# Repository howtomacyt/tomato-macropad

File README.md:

# tomato-macropad
This is my macropad that I somehow spent nearly 4 straight days designing!!!  
Felt very torturous at times but I am glad it's over and I've got something to show for all that work (hopefully)

## Features ##
9 customisable keys, 1 rotary encoder, 1 OLED Screen. 
Connect via USB-C. 

## CAD Model ##
Everything fits together using 4 M3 Bolts and heatset inserts. 4 for the case and PCB. 
It has 2 separate printed pieces.

**V2:**

## PCB ##
Experimented with RGB lights, but decided not to include them due to the added complexity in tracing. I also had difficulties implementing the firmware for it. 
I may consider switching to KMK. 

## Firmware ##
This hackpad uses QMK firmware. The keys are customisable. 

## Bill of Materials ##

- 9x Cherry MX Switches
- 9x DSA Keycaps
- 4x M3x5x4 Heatset inserts
- 4x M3x16mm SHCS Bolts
- 9x 1N4148 DO-35 Diodes
- 1x 0.91" 128x32 OLED Display
- 1x EC11 Rotary Encoder
- 1x XIAO RP2040

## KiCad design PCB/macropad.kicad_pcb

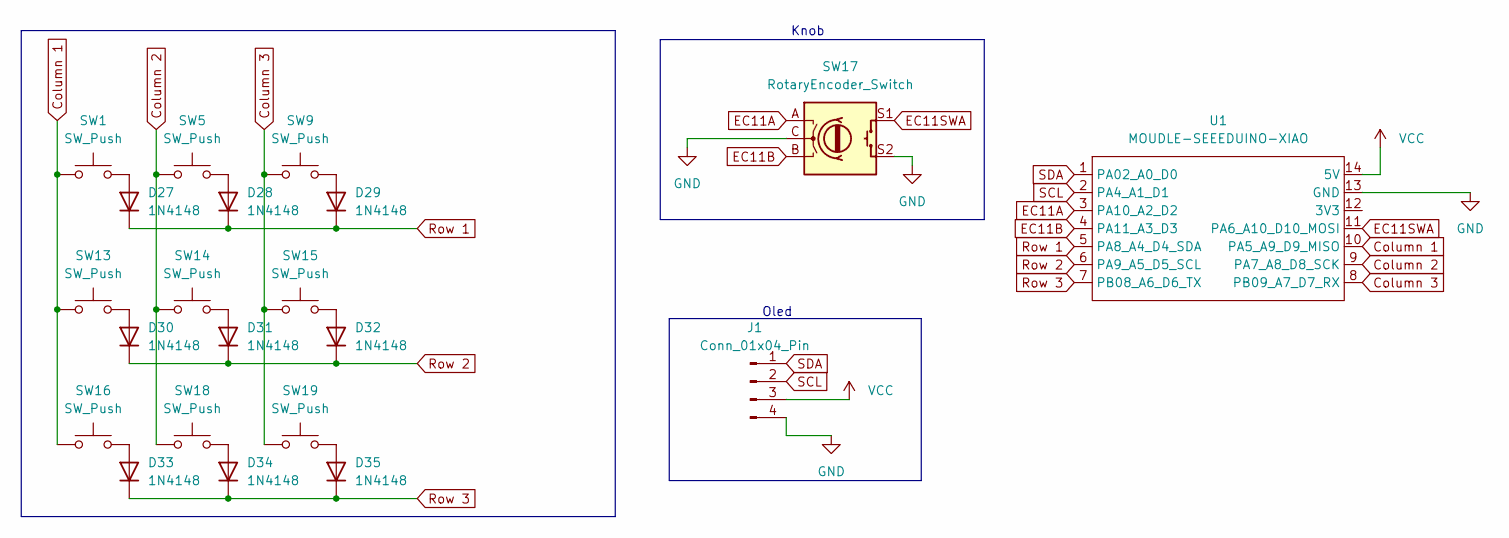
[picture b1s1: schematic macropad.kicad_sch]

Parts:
D27, D28, D29, D30, D31, D32, D33, D34, D35: 1N4148; D_DO-35_SOD27_P7.62mm_Horizontal
J1: Conn_01x04_Pin; PinHeader_1x04_P2.54mm_Vertical
SW1, SW5, SW9, SW13, SW14, SW15, SW16, SW18, SW19: SW_Push; SW_Cherry_MX_1.00u_PCB
SW17: RotaryEncoder_Switch; RotaryEncoder_Alps_EC11E-Switch_Vertical_H20mm
U1: MOUDLE-SEEEDUINO-XIAO; XIAO-Generic-Hybrid-14P-2.54-21X17.8MM

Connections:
Column 1: SW1.1, SW13.1, SW16.1, U1.10 (PA5_A9_D9_MISO)
Column 2: SW5.1, SW14.1, SW18.1, U1.9 (PA7_A8_D8_SCK)
Column 3: SW9.1, SW15.1, SW19.1, U1.8 (PB09_A7_D7_RX)
EC11A: SW17.A, U1.3 (PA10_A2_D2)
EC11B: SW17.B, U1.4 (PA11_A3_D3)
EC11SWA: SW17.S1, U1.11 (PA6_A10_D10_MOSI)
GND: J1.4, SW17.C, SW17.S2, U1.13 (GND)
unnamed: D27.2 (A), SW1.2
unnamed: D28.2 (A), SW5.2
unnamed: D29.2 (A), SW9.2
unnamed: D30.2 (A), SW13.2
unnamed: D31.2 (A), SW14.2
unnamed: D32.2 (A), SW15.2
unnamed: D33.2 (A), SW16.2
unnamed: D34.2 (A), SW18.2
unnamed: D35.2 (A), SW19.2
Row 1: D27.1 (K), D28.1 (K), D29.1 (K), U1.5 (PA8_A4_D4_SDA)
Row 2: D30.1 (K), D31.1 (K), D32.1 (K), U1.6 (PA9_A5_D5_SCL)
Row 3: D33.1 (K), D34.1 (K), D35.1 (K), U1.7 (PB08_A6_D6_TX)
SCL: J1.2, U1.2 (PA4_A1_D1)
SDA: J1.1, U1.1 (PA02_A0_D0)
VCC: J1.3, U1.14 (5V)

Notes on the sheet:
Oled
Knob

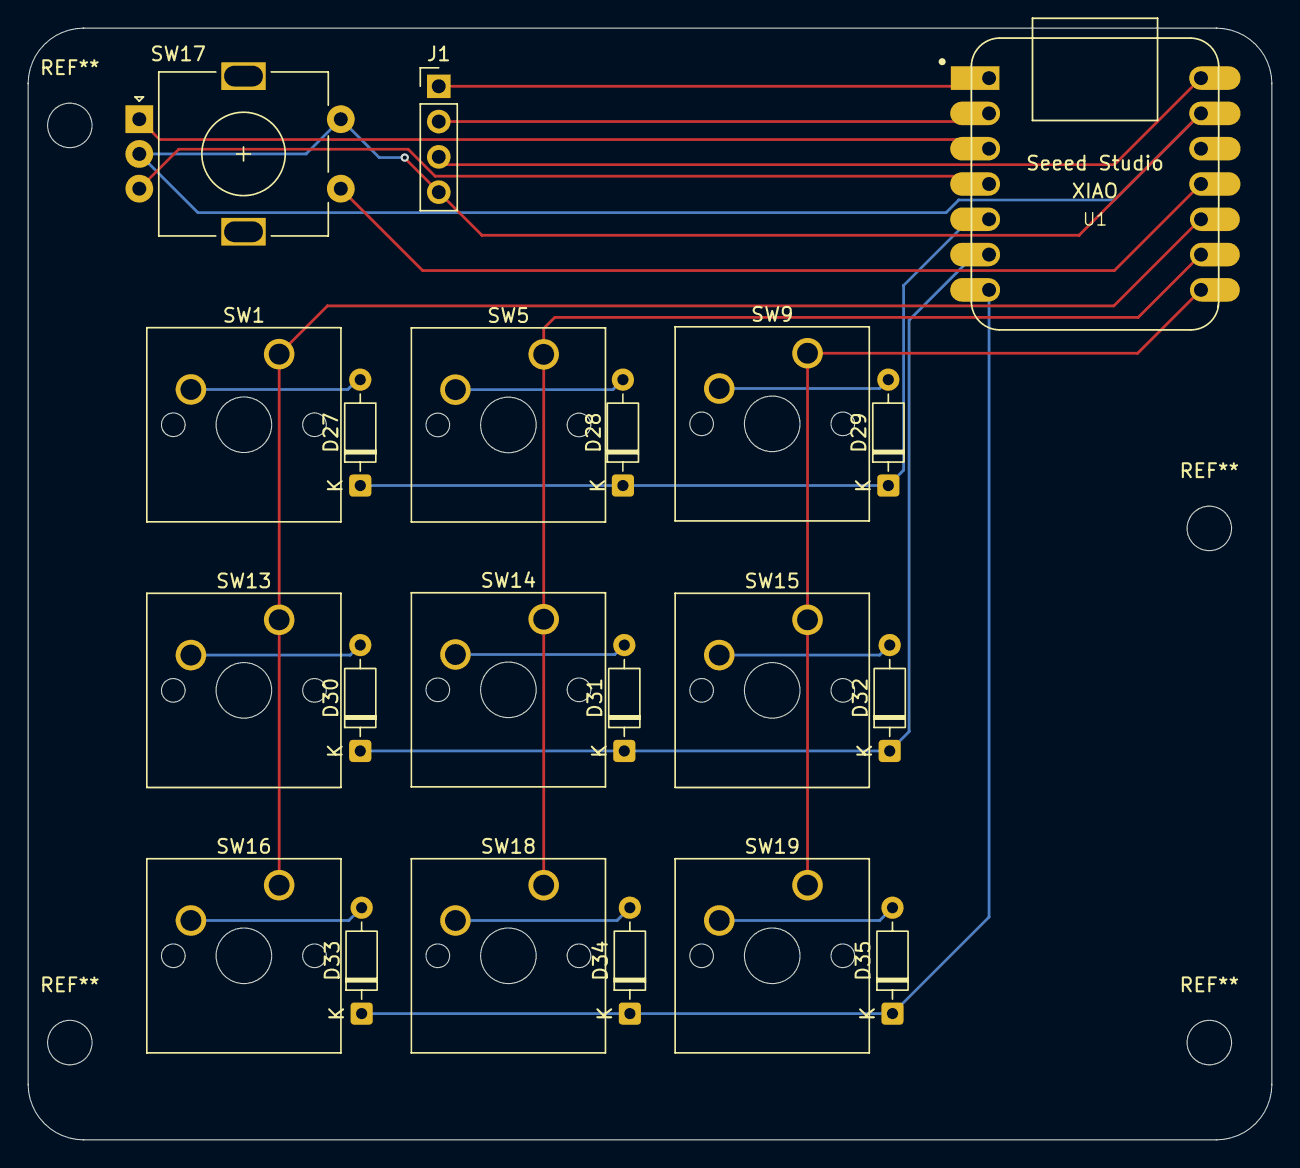
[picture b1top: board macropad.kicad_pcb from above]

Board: 2 copper layers, 89.5 x 80.0 mm, 21 parts (0 on the bottom side), 22 nets.

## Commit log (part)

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2026-03-30 finally done
2026-03-30 cad files
2026-03-30 cad file revised
